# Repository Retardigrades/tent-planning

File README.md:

# tent-planning

tent planning meta repo

This is for basic planning stuff and media files

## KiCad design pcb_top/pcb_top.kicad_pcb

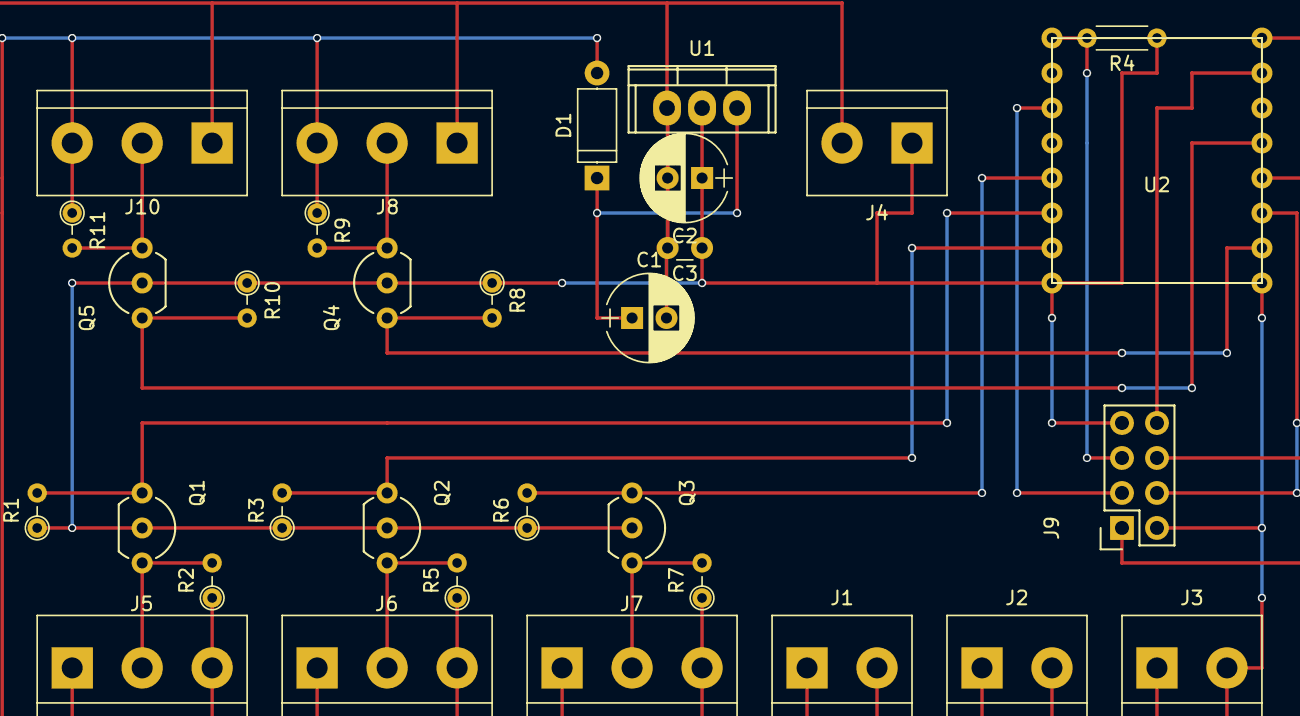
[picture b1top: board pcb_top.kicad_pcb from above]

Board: 2 copper layers, 32 parts (0 on the bottom side), 20 nets.

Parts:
C1, C2: 10µ; CP_Radial_D6.3mm_P2.50mm
C3: 100n; C_Disc_D3.0mm_W1.6mm_P2.50mm
D1: D; D_A-405_P7.62mm_Horizontal
J1, J2, J3, J4: Screw_Terminal_1x02; bornier2
J5, J6, J7, J8, J10: Screw_Terminal_1x03; bornier3
J9: CONN_02X04; Socket_Strip_Straight_2x04
Q1, Q2, Q3, Q4, Q5: 2N7000; TO-92_Inline_Wide
R1, R3, R6, R8, R10: 10K; R_Axial_DIN0204_L3.6mm_D1.6mm_P2.54mm_Vertical
R2, R5, R7, R9, R11: 3.3K; R_Axial_DIN0204_L3.6mm_D1.6mm_P2.54mm_Vertical
R4: 10K; R_Axial_DIN0204_L3.6mm_D1.6mm_P5.08mm_Horizontal
U1: LM1084IT-3.3/NOPB; TO-220
U2: ESP-12E; ESP_CUSTOM

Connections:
+3V3: C2.1, C3.1, J4.1, J9.7, Q1.2, Q2.2, Q3.2, Q4.2, Q5.2, R1.1, R3.1, R4.1, R6.1, R8.1, R10.1, U1.2, U2.8
+5V: D1.2, J1.1, J2.1, J3.1, J5.3, J6.3, J7.3, J8.3, J10.3, R2.1, R5.1, R7.1, R9.1, R11.1
CHPD: J9.3, U2.3
GND: C1.2, C2.2, C3.2, J1.2, J2.2, J3.2, J4.2, J5.1, J6.1, J7.1, J8.1, J9.2, J10.1, U1.1, U2.9
GPIO0: J9.6, U2.12
GPIO2: J9.4, U2.11
GPIO4: Q5.1, R10.2, U2.13
GPIO12: Q1.1, R1.2, U2.6
GPIO13: Q2.1, R3.2, U2.7
GPIO14: Q3.1, R6.2, U2.5
GPIO15: Q4.1, R8.2, U2.10
unnamed: C1.1, D1.1, U1.3
unnamed: J5.2, Q1.3, R2.2
unnamed: J6.2, Q2.3, R5.2
unnamed: J7.2, Q3.3, R7.2
unnamed: J8.2, Q4.3, R9.2
unnamed: J10.2, Q5.3, R11.2
RST: J9.5, R4.2, U2.1
RXD: J9.8, U2.15
TXD: J9.1, U2.16

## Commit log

2017-04-20 Make all so far produced files public.
2017-04-21 Add image with tent measurements
2017-05-05 Add technical overview doc
2017-05-19 Add led layout
2017-05-19 Fix missing led connection
2017-05-30 Add pcb schematic for top pcb
2017-05-31 Add pdf-print of top-pcb-schematic
2017-05-31 Update top-pcb schematic
2017-05-31 Add headphone amp Schematic
2017-05-31 Reorganizing connectors
2017-05-31 Set page title
2017-05-31 Name connectors
2017-05-31 Add schematic pdf print
2017-05-31 Update project file
2017-05-31 Rearange schematic
2017-05-31 New print
2017-05-31 Update project
2017-05-31 Add missing resistor value
2017-05-31 Rotate print
